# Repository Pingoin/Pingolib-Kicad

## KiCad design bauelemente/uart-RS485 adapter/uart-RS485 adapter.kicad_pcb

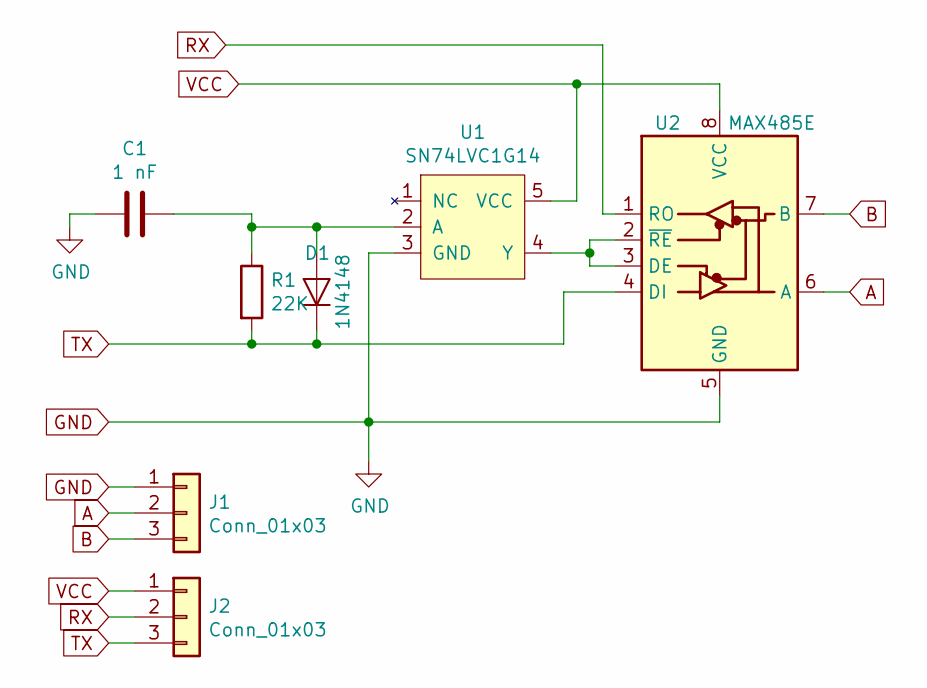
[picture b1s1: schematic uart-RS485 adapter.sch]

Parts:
C1: 1 nF; C_Disc_D5.0mm_W2.5mm_P2.50mm
D1: 1N4148; D_DO-35_SOD27_P7.62mm_Horizontal
J1, J2: Conn_01x03; PinHeader_1x03_P2.54mm_Vertical
R1: 22K; R_Axial_DIN0207_L6.3mm_D2.5mm_P7.62mm_Horizontal
U1: SN74LVC1G14; SOT-23-5_HandSoldering
U2: MAX485E; DIP-8_W7.62mm

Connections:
A: J1.2, U2.6 (A)
B: J1.3, U2.7 (B)
GND: C1.2, J1.1, U1.3 (GND), U2.5 (GND)
unnamed: C1.1, D1.2 (A), R1.1, U1.2 (A)
unnamed: U1.4 (Y), U2.2 (~RE), U2.3 (DE)
RX: J2.2, U2.1 (RO)
TX: D1.1 (K), J2.3, R1.2, U2.4 (DI)
VCC: J2.1, U1.5 (VCC), U2.8 (VCC)

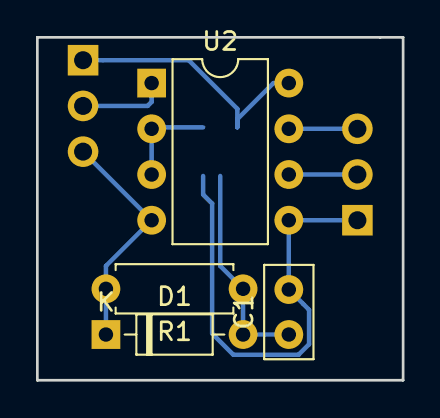
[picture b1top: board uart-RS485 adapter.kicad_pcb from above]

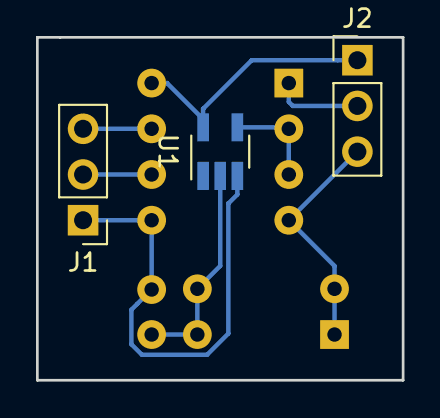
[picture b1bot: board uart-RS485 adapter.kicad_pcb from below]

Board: 2 copper layers, 20.3 x 19.1 mm, 7 parts (3 on the bottom side), 8 nets.

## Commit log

2018-12-08 Spannungswandler6x8 (Footprint und Symbol/Modell unter Komplexes) HohlsteckerTHT5,5x2,1.kicad_mod SicherungshalterTHT5x20.kicad_mod PrintklemmeMKDSN-1,5-12x5,08.kicad_mod
2018-12-08 Fehler an 3d-Pfad behoben
2018-12-21 Spannungswandler6x8.kicad_mod anpassung bauteilgrenzen
2019-03-07 arduinos und uart adapter
2019-12-05 ESP-Module hinzugefügt Überarbeitung der Struktur
